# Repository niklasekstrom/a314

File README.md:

# A314

## What is it?

*A314* is a family of expansions for Amiga computers that lets a Raspberry Pi
(RPi) be used as a co-processor to the Amiga.

The Amiga and the RPi communicate through a shared memory that resides on the
A314 board. A communication protocol is implemented on top of the shared memory,
that allows programs on the Amiga to establish logical communication channels to
*services* running on the RPi. The protocol is handled by drivers on each side,
[*a314.device*](Software/a314device) on the Amiga and [*a314d*](Software/a314d)
on the RPi. The drivers are responsible for multiplexing packets from the logical
channels and notifying the receiving side when a packet is available, using interrupts.

## Hardware variants

Initially there was a single variant of A314 that connected to the trapdoor
on an Amiga 500. Since then several more variants have been developed for
different Amiga models. The same software run on the different hardware variants.

The design files for the different hardware variants are available in separate
repositories. The currently available variants are:

| Variant | Amiga model | Connector | GitHub repository |
|---------|-------------|-----------|-------------------|
| A314-500 | Amiga 500 | Trapdoor | <https://github.com/Eriond/A314-500-PCB> |
| A314-600 | Amiga 600 | Trapdoor | <https://github.com/Eriond/A314-600-PCB> |
| A314-1000 | Amiga 1000 | Front expansion | <https://github.com/Eriond/A314-1000-PCB> |
| A314-cp | Any Amiga with clockport | Clockport | <https://github.com/niklasekstrom/clockport_pi_interface> <br/> <https://github.com/Eriond/clockport_pi_interface> (alternative PCB layout) |

|         |            |
| ------------- |---------------|
|  |  |
|  |  |

The A314 software has also been adapted to run on the Musashi version of
[PiStorm](https://github.com/captain-amygdala/pistorm).

## What can you do with it today?

We have implemented a few services that run on the RPi and on the Amiga:

- [*a314fs*](Software/a314fs) is a file system that is mounted in AmigaDOS as the PI0: device.
The volume in PI0: is called PiDisk:, and is mapped to a directory in the RPi.

- [*pi*](Software/picmd) is a command that lets you invoke executables on the RPi from the AmigaDOS CLI. For example, if your current working directory is on PiDisk: and you run `pi vc hello.c -o hello`, then the vc program (the VBCC cross-compiler) is executed on the RPi with the given arguments. It will cross-compile `hello.c` into the Amiga executable file `hello`. The resulting binary is immediately accessible through the a314fs.  
You may also launch Interactive applications using the pi command, such as `pi mc -a` which will run Midnight Commander. Running pi without any arguments is equivalent to `pi bash` and will present you with a bash prompt from the RPi.

|         |            |
| ------------- |---------------|
|   |  |

- [*PiAudio*](Software/piaudio) lets the RPi stream audio samples directly to the shared chip memory, from where Paula plays those samples. PiAudio is integrated with [ALSA](https://www.alsa-project.org) on the RPi so that any program that plays audio through ALSA can be used, i.e. "pi mpg123 -a amiga song.mp3" plays song.mp3 using the program mpg123 to the Amiga.

- [*RemoteWB*](Software/remotewb) works by moving the Workbench bitplanes over to the chip memory on the A314. This requires that the A500 has at least a 8372 Agnus. During drawing of each frame on the Amiga, the RPi reads those bitplanes, encodes them into a [GIF image](Software/bpls2gif), and transmits that image to a web browser through a web socket. The web browser in turn, returns key presses and mouse movements back to the Amiga through the same web socket. In effect, this becomes a web browser based remote control application, comparable to VNC but with near zero performance impact on the Amiga CPU!

- [*VideoPlayer*](Software/videoplayer) is a simple program that displays a sequence of images on the A500 by letting the RPi write bitplanes directly to the shared memory (this again requires that the A314 memory is chip memory, and not "ranger" memory).

- [*a314eth.device*](Software/ethernet) is a SANA-II driver that forwards Ethernet packets to the network interface of the RPi. Together with an Amiga TCP/IP stack this provides network access to the Amiga.

- [*a314disk.device*](Software/disk) mounts an ADF or HDF file on the RPi as a disk drive on the Amiga.

- [*PiHid*](Software/hid) takes input events from mouse and keyboard that are
connected to the RPI with USB, and forwards those input events to input.device
in the Amiga.

- [*PiStats*](Software/pistats) displays live Raspberry Pi statistics on the Amiga, including per-core CPU usage, memory, kernel version, and root filesystem usage. It supports console output and graphical interfaces.

- [*a314sh*](Software/a314sh) lets you run AmigaDOS commands from the Raspberry Pi. Its Amiga-side daemon keeps a persistent shell context and returns command output and status to the Pi.

## What could it potentially be used for in the future?

Here are some services that we have considered but not gotten around to implement:

- Networking through a *bsdsocket.library* implementation that forwards socket operations to the RPi and executes those operations there. This would give a higher degree of offloading than using the SANA-II driver with a TCP/IP stack running on the Amiga. The start of such a service is available
in the `libremote` branch.

- Your ideas?

## Do you want to get involved?

If this sounds interesting, you'll probably want an A314 of your own to play with.
All the information needed to build boards is freely available in the hardware
GitHub repositories linked to above.

The source code for the A314 software that runs on the Amiga and on the RPi is
available in the [Software](Software) directory.

There is a Discord server for discussing A314. [Here's the invite link](https://discord.gg/TGZNKnA).

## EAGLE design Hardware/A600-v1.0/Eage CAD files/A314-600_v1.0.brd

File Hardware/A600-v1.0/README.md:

# A314-600 PCB v1.0

## Changelog

Initial commit of the **Amiga 600** version of the A314 board. Main differences compared to the Amiga 500 version:
 - 2MB chipRAM available as A314 shared memory (Disables the motherboard RAM)
 - Mechanical restrictions of the expansion bay implies Raspberry *Zero* form factor. The low power consumption and more generous voltage tolerances of the Zero* allowed for a simpler design, elliminating the 5V DC/DC converter (IC11 & Co.). 
 *see: https://raspberry-projects.com/pi/pi-hardware/raspberry-pi-zero/raspberry-pi-zero-hardware-general-specifications
  - Replacement LED board included. Allows for distinction between HardDrive and A314 activity on the same LED (Bi-colour)
 - Original LED overlay. If you don't want to use the included replacement LED board, then use your existing one, but connect it through the A314! A314 activity is then multiplexed on the HDD LED.
## Notes
This PCB has NPT milled slots with a narrow width (1.5mm) which some board houses won't accept. I have successfully used WellPCB with excellent results. Check with you favourite board house if they accept such narrow slots, before submitting a job.
At the moment of writing, AllPCB and JLCPCB could not handle this PCB. This may change in the future.

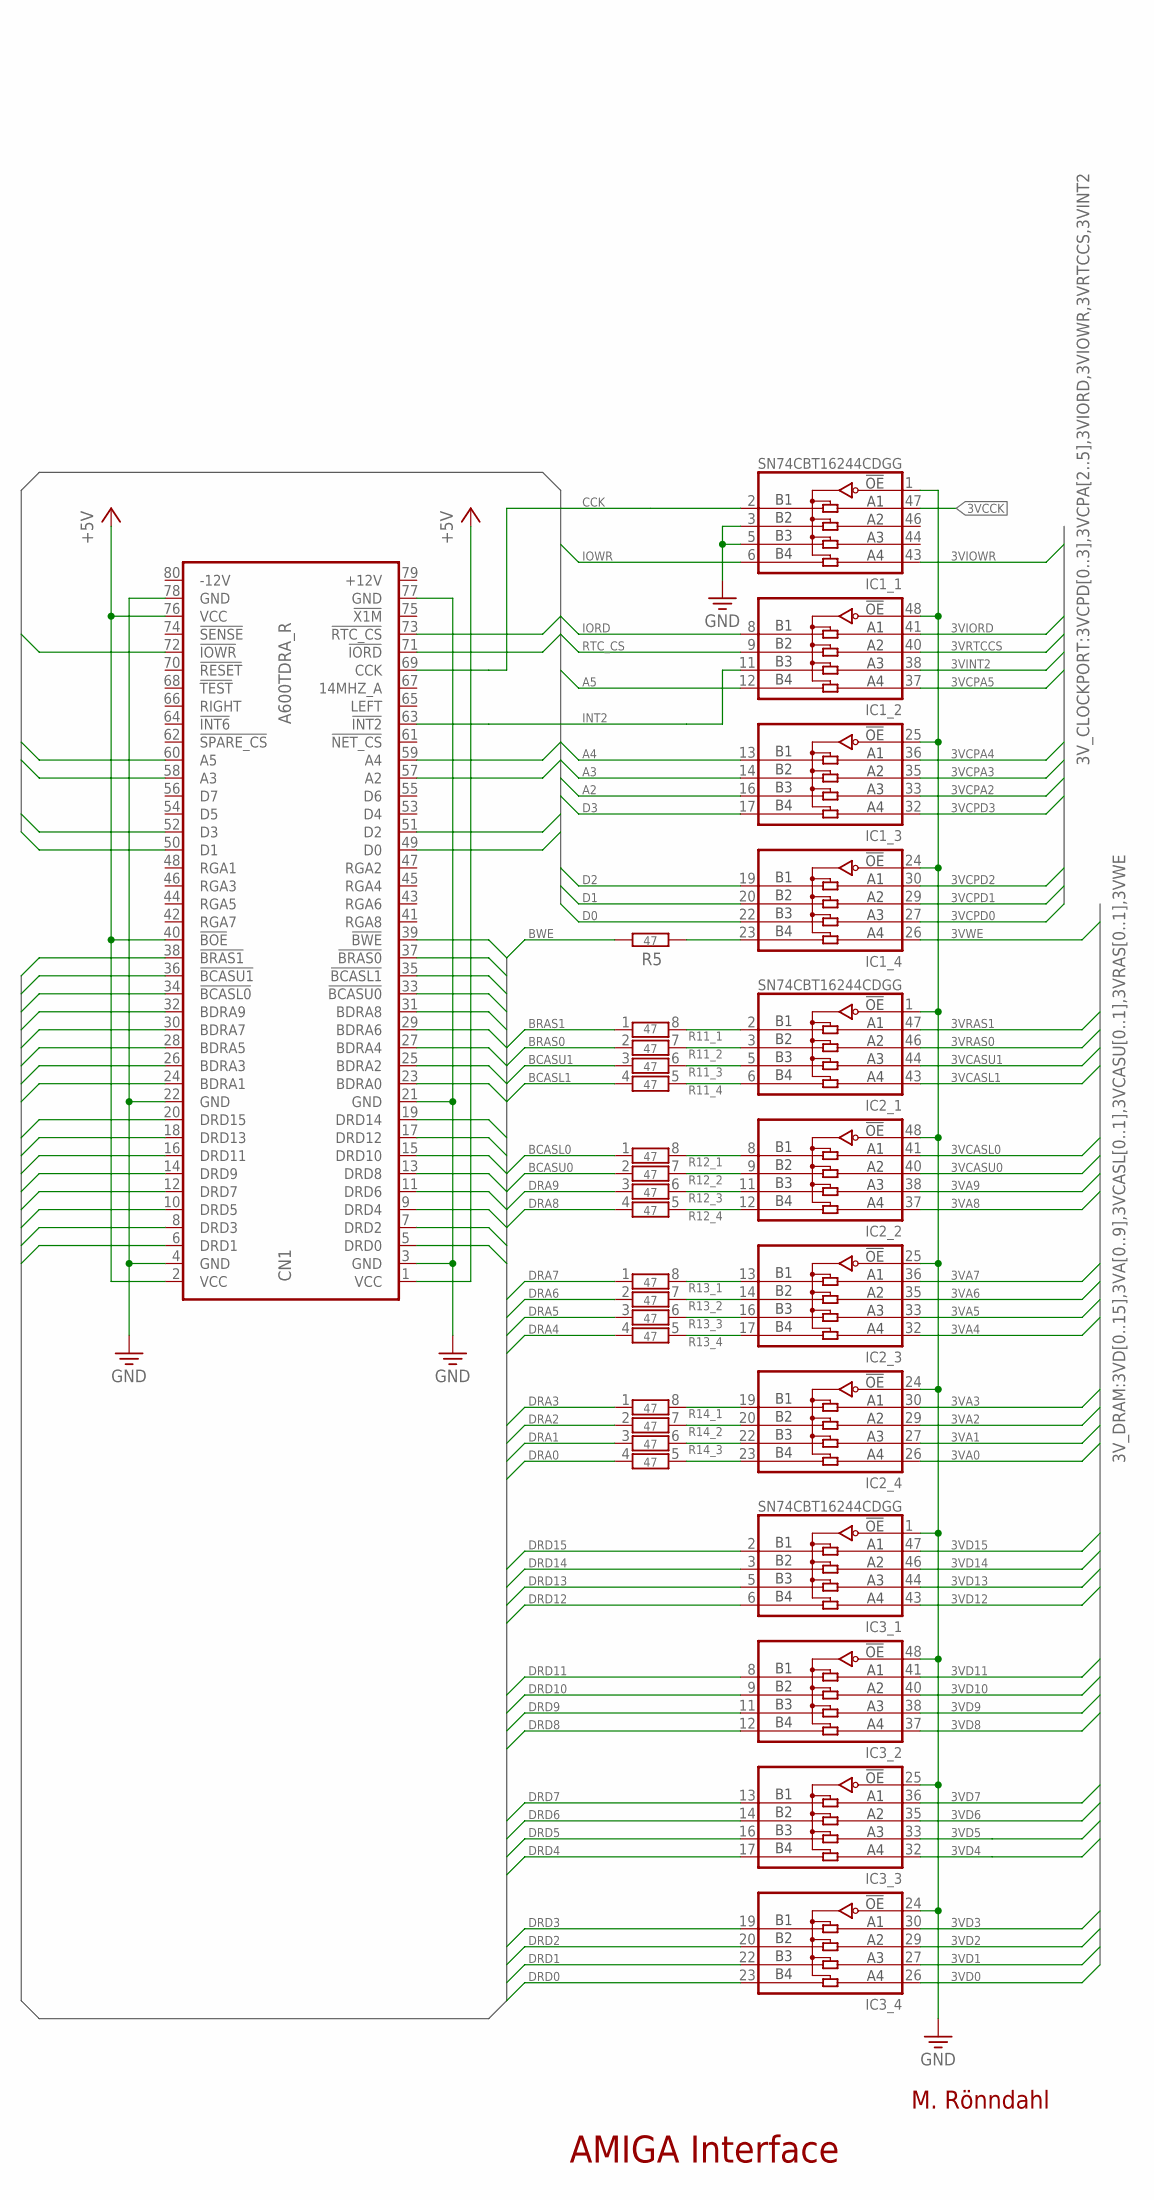
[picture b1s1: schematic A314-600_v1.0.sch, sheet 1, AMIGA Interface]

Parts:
CN1: A600TDRA_R; CE-2X40_1.27_R
IC1, IC2, IC3: SN74CBT16244CDGG; PSOP-DGG48
R5: 47; R0603
R11, R12, R13, R14: 47; CTS742C083

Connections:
3VA0: IC2.26 (A4); also elsewhere on the board
3VA1: IC2.27 (A3); also elsewhere on the board
3VA2: IC2.29 (A2); also elsewhere on the board
3VA3: IC2.30 (A1); also elsewhere on the board
3VA4: IC2.32 (A4); also elsewhere on the board
3VA5: IC2.33 (A3); also elsewhere on the board
3VA6: IC2.35 (A2); also elsewhere on the board
3VA7: IC2.36 (A1); also elsewhere on the board
3VA8: IC2.37 (A4); also elsewhere on the board
3VA9: IC2.38 (A3); also elsewhere on the board
3VCASL0: IC2.41 (A1); also elsewhere on the board
3VCASL1: IC2.43 (A4); also elsewhere on the board
3VCASU0: IC2.40 (A2); also elsewhere on the board
3VCASU1: IC2.44 (A3); also elsewhere on the board
3VCCK: IC1.47 (A1); also elsewhere on the board
3VCPA2: IC1.33 (A3); also elsewhere on the board
3VCPA3: IC1.35 (A2); also elsewhere on the board
3VCPA4: IC1.36 (A1); also elsewhere on the board
3VCPA5: IC1.37 (A4); also elsewhere on the board
3VCPD0: IC1.27 (A3); also elsewhere on the board
3VCPD1: IC1.29 (A2); also elsewhere on the board
3VCPD2: IC1.30 (A1); also elsewhere on the board
3VCPD3: IC1.32 (A4); also elsewhere on the board
3VD0: IC3.26 (A4); also elsewhere on the board
3VD1: IC3.27 (A3); also elsewhere on the board
3VD2: IC3.29 (A2); also elsewhere on the board
3VD3: IC3.30 (A1); also elsewhere on the board
3VD4: IC3.32 (A4); also elsewhere on the board
3VD5: IC3.33 (A3); also elsewhere on the board
3VD6: IC3.35 (A2); also elsewhere on the board
3VD7: IC3.36 (A1); also elsewhere on the board
3VD8: IC3.37 (A4); also elsewhere on the board
3VD9: IC3.38 (A3); also elsewhere on the board
3VD10: IC3.40 (A2); also elsewhere on the board
3VD11: IC3.41 (A1); also elsewhere on the board
3VD12: IC3.43 (A4); also elsewhere on the board
3VD13: IC3.44 (A3); also elsewhere on the board
3VD14: IC3.46 (A2); also elsewhere on the board
3VD15: IC3.47 (A1); also elsewhere on the board
3VINT2: IC1.38 (A3); also elsewhere on the board
3VIORD: IC1.41 (A1); also elsewhere on the board
3VIOWR: IC1.43 (A4); also elsewhere on the board
3VRAS0: IC2.46 (A2); also elsewhere on the board
3VRAS1: IC2.47 (A1); also elsewhere on the board
3VRTCCS: IC1.40 (A2); also elsewhere on the board
3VWE: IC1.26 (A4); also elsewhere on the board
+5V: CN1.1 (VCC), CN1.2 (VCC), CN1.40 (!BOE), CN1.76 (VCC); also elsewhere on the board
A2: CN1.57 (A2), IC1.16 (B3)
A3: CN1.58 (A3), IC1.14 (B2)
A4: CN1.59 (A4), IC1.13 (B1)
A5: CN1.60 (A5), IC1.12 (B4)
BCASL0: CN1.34 (!BCASL0), R12.1
BCASL1: CN1.35 (!BCASL1), R11.4
BCASU0: CN1.33 (!BCASU0), R12.2
BCASU1: CN1.36 (!BCASU1), R11.3
BRAS0: CN1.37 (!BRAS0), R11.2
BRAS1: CN1.38 (!BRAS1), R11.1
BWE: CN1.39 (!BWE), R5.1
CCK: CN1.69 (CCK), IC1.2 (B1)
D0: CN1.49 (D0), IC1.22 (B3)
D1: CN1.50 (D1), IC1.20 (B2)
D2: CN1.51 (D2), IC1.19 (B1)
D3: CN1.52 (D3), IC1.17 (B4)
DRA0: CN1.23 (BDRA0), R14.4
DRA1: CN1.24 (BDRA1), R14.3
DRA2: CN1.25 (BDRA2), R14.2
DRA3: CN1.26 (BDRA3), R14.1
DRA4: CN1.27 (BDRA4), R13.4
DRA5: CN1.28 (BDRA5), R13.3
DRA6: CN1.29 (BDRA6), R13.2
DRA7: CN1.30 (BDRA7), R13.1
DRA8: CN1.31 (BDRA8), R12.4
DRA9: CN1.32 (BDRA9), R12.3
DRD0: CN1.5 (DRD0), IC3.23 (B4)
DRD1: CN1.6 (DRD1), IC3.22 (B3)
DRD2: CN1.7 (DRD2), IC3.20 (B2)
DRD3: CN1.8 (DRD3), IC3.19 (B1)
DRD4: CN1.9 (DRD4), IC3.17 (B4)
DRD5: CN1.10 (DRD5), IC3.16 (B3)
DRD6: CN1.11 (DRD6), IC3.14 (B2)
DRD7: CN1.12 (DRD7), IC3.13 (B1)
DRD8: CN1.13 (DRD8), IC3.12 (B4)
DRD9: CN1.14 (DRD9), IC3.11 (B3)
DRD10: CN1.15 (DRD10), IC3.9 (B2)
DRD11: CN1.16 (DRD11), IC3.8 (B1)
DRD12: CN1.17 (DRD12), IC3.6 (B4)
DRD13: CN1.18 (DRD13), IC3.5 (B3)
DRD14: CN1.19 (DRD14), IC3.3 (B2)
DRD15: CN1.20 (DRD15), IC3.2 (B1)
GND: CN1.3 (GND), CN1.4 (GND), CN1.21 (GND), CN1.22 (GND), CN1.77 (GND), CN1.78 (GND), IC1.1 (!OE), IC1.3 (B2), IC1.5 (B3), IC1.24 (!OE), IC1.25 (!OE), IC1.48 (!OE), IC2.1 (!OE), IC2.24 (!OE), IC2.25 (!OE), IC2.48 (!OE), IC3.1 (!OE), IC3.24 (!OE), IC3.25 (!OE), IC3.48 (!OE); also elsewhere on the board
INT2: CN1.63 (!INT2), IC1.11 (B3)
IORD: CN1.71 (!IORD), IC1.8 (B1)
IOWR: CN1.72 (!IOWR), IC1.6 (B4)
unnamed: IC2.23 (B4), R14.5
unnamed: IC2.22 (B3), R14.6
unnamed: IC2.20 (B2), R14.7
unnamed: IC2.19 (B1), R14.8
unnamed: IC2.17 (B4), R13.5
unnamed: IC2.16 (B3), R13.6
unnamed: IC2.14 (B2), R13.7
unnamed: IC2.13 (B1), R13.8
unnamed: IC2.12 (B4), R12.5
unnamed: IC2.11 (B3), R12.6
unnamed: IC2.9 (B2), R12.7
unnamed: IC2.8 (B1), R12.8
unnamed: IC2.6 (B4), R11.5
unnamed: IC2.5 (B3), R11.6
unnamed: IC2.3 (B2), R11.7
unnamed: IC2.2 (B1), R11.8
unnamed: IC1.23 (B4), R5.2
RTC_CS: CN1.73 (!RTC_CS), IC1.9 (B2)

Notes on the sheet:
AMIGA Interface
M. Rönndahl

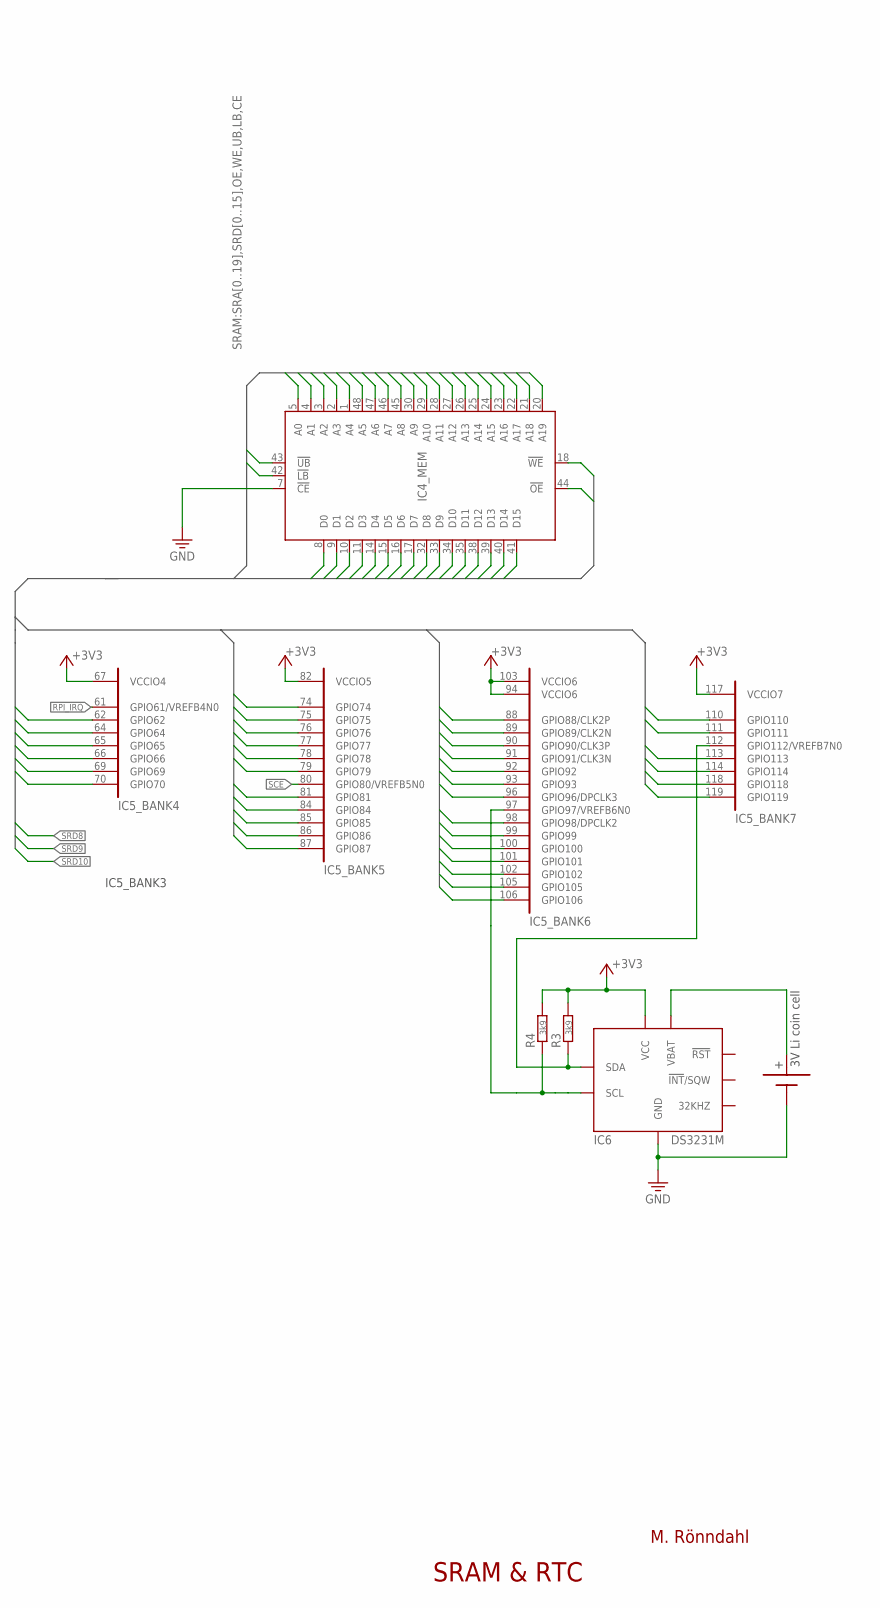
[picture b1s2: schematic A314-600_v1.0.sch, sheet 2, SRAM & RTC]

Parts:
BAT1: CR2025/CR2032TH; LINX20XX-THM
IC4: IS61WV102416FBLL-TLI; TSOP-1_48L_12X20
IC5: 10M08SCE144; SQFP-S-20X20-144
IC6: DS3231M; SOIC8
R3, R4: 3k9; R0603

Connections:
+: BAT1.+@1 (+), BAT1.+@2 (+), BAT1.+@3 (+), BAT1.+@4 (+), IC6.6 (VBAT)
+3V3: IC5.67 (VCCIO4), IC5.82 (VCCIO5), IC5.94 (VCCIO6), IC5.103 (VCCIO6), IC5.117 (VCCIO7), IC6.2 (VCC), R3.2, R4.2; also elsewhere on the board
GND: BAT1.GND (-), IC4.7 (!CE), IC6.5 (GND); also elsewhere on the board
LB: IC4.42 (!LB), IC5.79 (GPIO79)
OE: IC4.44 (!OE), IC5.84 (GPIO84)
RPI_IRQ: IC5.61 (GPIO61/VREFB4N0); also elsewhere on the board
RTC_SCL: IC5.97 (GPIO97/VREFB6N0), IC6.8 (SCL), R4.1
RTC_SDA: IC5.112 (GPIO112/VREFB7N0), IC6.7 (SDA), R3.1
SCE: IC5.80 (GPIO80/VREFB5N0); also elsewhere on the board
SRA0: IC4.5 (A0), IC5.93 (GPIO93)
SRA1: IC4.4 (A1), IC5.92 (GPIO92)
SRA2: IC4.3 (A2), IC5.91 (GPIO91/CLK3N)
SRA3: IC4.2 (A3), IC5.90 (GPIO90/CLK3P)
SRA4: IC4.1 (A4), IC5.89 (GPIO89/CLK2N)
SRA5: IC4.48 (A5), IC5.88 (GPIO88/CLK2P)
SRA6: IC4.47 (A6), IC5.87 (GPIO87)
SRA7: IC4.46 (A7), IC5.86 (GPIO86)
SRA8: IC4.45 (A8), IC5.85 (GPIO85)
SRA9: IC4.30 (A9), IC5.62 (GPIO62)
SRA10: IC4.29 (A10), IC5.64 (GPIO64)
SRA11: IC4.28 (A11), IC5.65 (GPIO65)
SRA12: IC4.27 (A12), IC5.66 (GPIO66)
SRA13: IC4.26 (A13), IC5.69 (GPIO69)
SRA14: IC4.25 (A14), IC5.70 (GPIO70)
SRA15: IC4.24 (A15), IC5.110 (GPIO110)
SRA16: IC4.23 (A16), IC5.111 (GPIO111)
SRA17: IC4.22 (A17), IC5.113 (GPIO113)
SRA18: IC4.21 (A18), IC5.114 (GPIO114)
SRA19: IC4.20 (A19), IC5.118 (GPIO118)
SRD0: IC4.8 (D0), IC5.96 (GPIO96/DPCLK3)
SRD1: IC4.9 (D1), IC5.98 (GPIO98/DPCLK2)
SRD2: IC4.10 (D2), IC5.99 (GPIO99)
SRD3: IC4.11 (D3), IC5.100 (GPIO100)
SRD4: IC4.14 (D4), IC5.101 (GPIO101)
SRD5: IC4.15 (D5), IC5.102 (GPIO102)
SRD6: IC4.16 (D6), IC5.105 (GPIO105)
SRD7: IC4.17 (D7), IC5.106 (GPIO106)
SRD8: IC4.32 (D8); also elsewhere on the board
SRD9: IC4.33 (D9); also elsewhere on the board
SRD10: IC4.34 (D10); also elsewhere on the board
SRD11: IC4.35 (D11), IC5.74 (GPIO74)
SRD12: IC4.38 (D12), IC5.75 (GPIO75)
SRD13: IC4.39 (D13), IC5.76 (GPIO76)
SRD14: IC4.40 (D14), IC5.77 (GPIO77)
SRD15: IC4.41 (D15), IC5.78 (GPIO78)
UB: IC4.43 (!UB), IC5.81 (GPIO81)
WE: IC4.18 (!WE), IC5.119 (GPIO119)

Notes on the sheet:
IC5_BANK3
SRAM & RTC
3V Li coin cell
M. Rönndahl

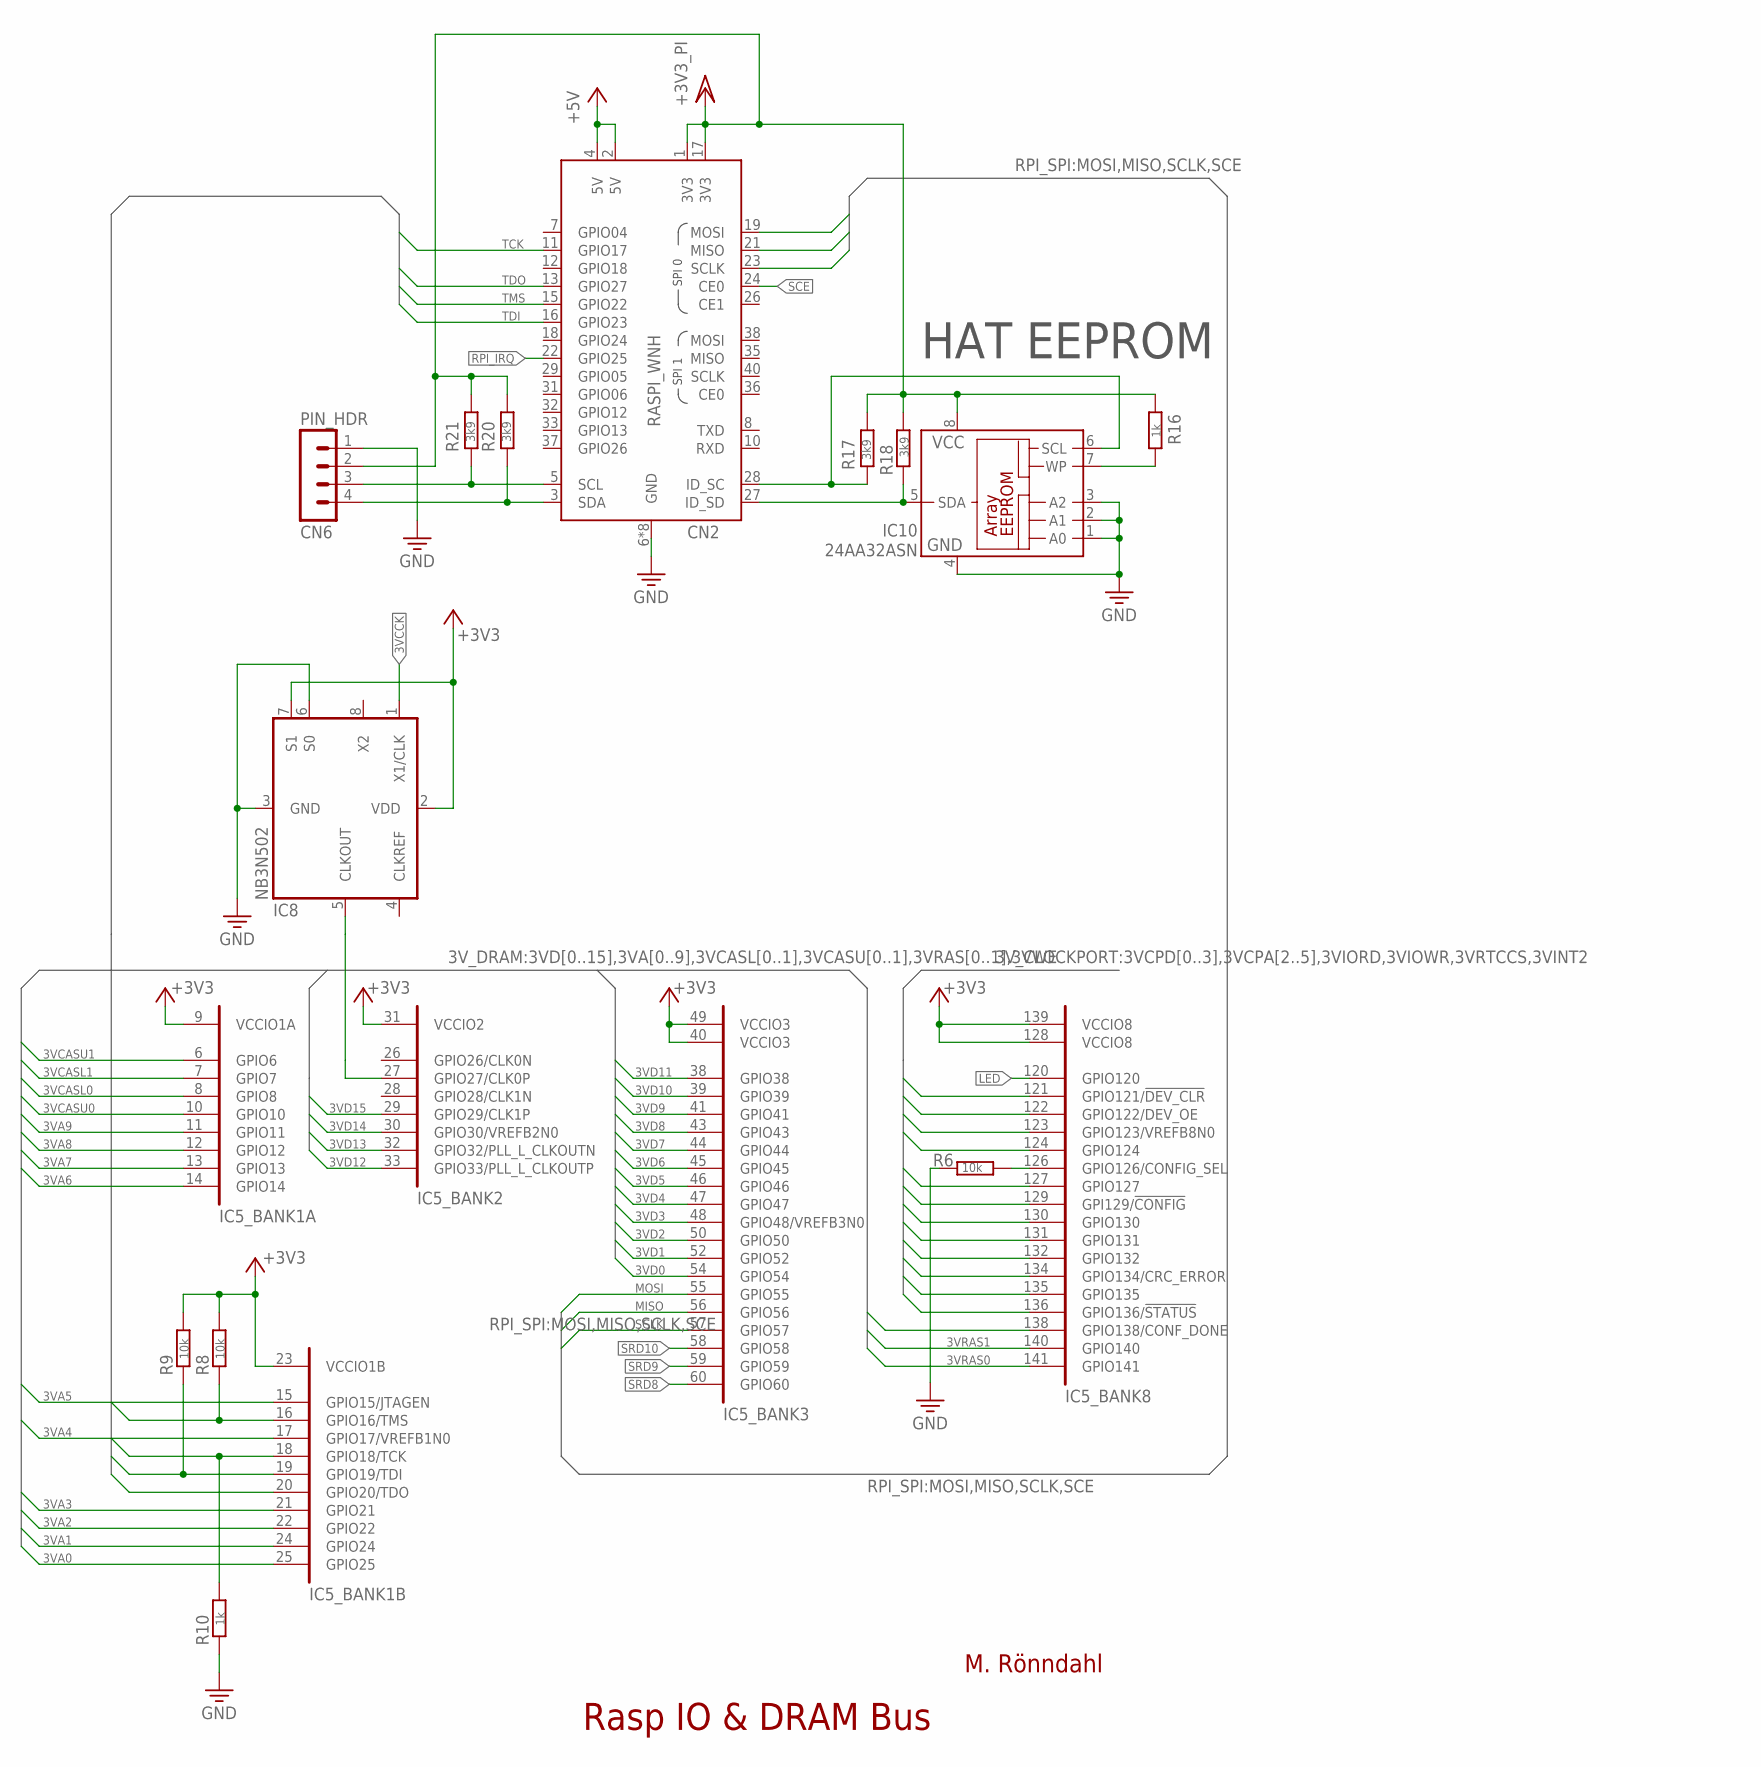
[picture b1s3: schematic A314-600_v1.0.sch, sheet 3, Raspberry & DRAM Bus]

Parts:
CN2: RASPI_WNH; RASPBERRYPIZEROW_NO_HOLES
CN6: PIN_HDR; MA04-1
IC5: 10M08SCE144; SQFP-S-20X20-144
IC8: NB3N502; SO08
IC10: 24AA32ASN; SO-08
R6, R8, R9: 10k; R0603
R10, R16: 1k; R0603
R17, R18, R20, R21: 3k9; R0603

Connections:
3VA0: IC5.25 (GPIO25); also elsewhere on the board
3VA1: IC5.24 (GPIO24); also elsewhere on the board
3VA2: IC5.22 (GPIO22); also elsewhere on the board
3VA3: IC5.21 (GPIO21); also elsewhere on the board
3VA4: IC5.17 (GPIO17/VREFB1N0); also elsewhere on the board
3VA5: IC5.15 (GPIO15/JTAGEN); also elsewhere on the board
3VA6: IC5.14 (GPIO14); also elsewhere on the board
3VA7: IC5.13 (GPIO13); also elsewhere on the board
3VA8: IC5.12 (GPIO12); also elsewhere on the board
3VA9: IC5.11 (GPIO11); also elsewhere on the board
3VCASL0: IC5.8 (GPIO8); also elsewhere on the board
3VCASL1: IC5.7 (GPIO7); also elsewhere on the board
3VCASU0: IC5.10 (GPIO10); also elsewhere on the board
3VCASU1: IC5.6 (GPIO6); also elsewhere on the board
3VCCK: IC8.1 (X1/CLK); also elsewhere on the board
3VCPA2: IC5.131 (GPIO131); also elsewhere on the board
3VCPA3: IC5.130 (GPIO130); also elsewhere on the board
3VCPA4: IC5.129 (GPI129/!CONFIG); also elsewhere on the board
3VCPA5: IC5.127 (GPIO127); also elsewhere on the board
3VCPD0: IC5.136 (GPIO136/!STATUS); also elsewhere on the board
3VCPD1: IC5.135 (GPIO135); also elsewhere on the board
3VCPD2: IC5.134 (GPIO134/CRC_ERROR); also elsewhere on the board
3VCPD3: IC5.132 (GPIO132); also elsewhere on the board
3VD0: IC5.54 (GPIO54); also elsewhere on the board
3VD1: IC5.52 (GPIO52); also elsewhere on the board
3VD2: IC5.50 (GPIO50); also elsewhere on the board
3VD3: IC5.48 (GPIO48/VREFB3N0); also elsewhere on the board
3VD4: IC5.47 (GPIO47); also elsewhere on the board
3VD5: IC5.46 (GPIO46); also elsewhere on the board
3VD6: IC5.45 (GPIO45); also elsewhere on the board
3VD7: IC5.44 (GPIO44); also elsewhere on the board
3VD8: IC5.43 (GPIO43); also elsewhere on the board
3VD9: IC5.41 (GPIO41); also elsewhere on the board
3VD10: IC5.39 (GPIO39); also elsewhere on the board
3VD11: IC5.38 (GPIO38); also elsewhere on the board
3VD12: IC5.33 (GPIO33/PLL_L_CLKOUTP); also elsewhere on the board
3VD13: IC5.32 (GPIO32/PLL_L_CLKOUTN); also elsewhere on the board
3VD14: IC5.30 (GPIO30/VREFB2N0); also elsewhere on the board
3VD15: IC5.29 (GPIO29/CLK1P); also elsewhere on the board
3VINT2: IC5.124 (GPIO124); also elsewhere on the board
3VIORD: IC5.122 (GPIO122/DEV_OE); also elsewhere on the board
3VIOWR: IC5.121 (GPIO121/!DEV_CLR); also elsewhere on the board
3VRAS0: IC5.141 (GPIO141); also elsewhere on the board
3VRAS1: IC5.140 (GPIO140); also elsewhere on the board
3VRTCCS: IC5.123 (GPIO123/VREFB8N0); also elsewhere on the board
3VWE: IC5.138 (GPIO138/CONF_DONE); also elsewhere on the board
14MHZ: IC5.27 (GPIO27/CLK0P), IC8.5 (CLKOUT)
+3V3: IC5.9 (VCCIO1A), IC5.23 (VCCIO1B), IC5.31 (VCCIO2), IC5.40 (VCCIO3), IC5.49 (VCCIO3), IC5.128 (VCCIO8), IC5.139 (VCCIO8), IC8.2 (VDD), IC8.7 (S1), R8.2, R9.2; also elsewhere on the board
+5V: CN2.2 (5V), CN2.4 (5V); also elsewhere on the board
CONF_SEL: IC5.126 (GPIO126/CONFIG_SEL), R6.1
GND: CN2.6 (GND), CN2.9 (GND), CN2.14 (GND), CN2.20 (GND), CN2.25 (GND), CN2.30 (GND), CN2.34 (GND), CN2.39 (GND), CN6.1, IC8.3 (GND), IC8.6 (S0), IC10.1 (A0), IC10.2 (A1), IC10.3 (A2), IC10.4 (GND), R6.2, R10.1; also elsewhere on the board
HAT_SCL: CN2.28 (ID_SC), IC10.6 (SCL), R17.2
HAT_SDA: CN2.27 (ID_SD), IC10.5 (SDA), R18.1
LED: IC5.120 (GPIO120); also elsewhere on the board
MISO: CN2.21 (MISO), IC5.56 (GPIO56)
MOSI: CN2.19 (MOSI), IC5.55 (GPIO55)
PI_SCL: CN2.5 (SCL), CN6.3, R21.2
PI_SDA: CN2.3 (SDA), CN6.4, R20.2
RPI_IRQ: CN2.22 (GPIO25); also elsewhere on the board
SCE: CN2.24 (CE0); also elsewhere on the board
SCLK: CN2.23 (SCLK), IC5.57 (GPIO57)
SRD8: IC5.60 (GPIO60); also elsewhere on the board
SRD9: IC5.59 (GPIO59); also elsewhere on the board
SRD10: IC5.58 (GPIO58); also elsewhere on the board
TCK: CN2.11 (GPIO17), IC5.18 (GPIO18/TCK), R10.2
TDI: CN2.16 (GPIO23), IC5.19 (GPIO19/TDI), R9.1
TDO: CN2.13 (GPIO27), IC5.20 (GPIO20/TDO)
TMS: CN2.15 (GPIO22), IC5.16 (GPIO16/TMS), R8.1
VCC/2: CN2.1 (3V3), CN2.17 (3V3), CN6.2, IC10.8 (VCC), R16.2, R17.1, R18.2, R20.1, R21.1; also elsewhere on the board
WP: IC10.7 (WP), R16.1

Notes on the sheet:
Rasp IO & DRAM Bus
M. Rönndahl
HAT EEPROM

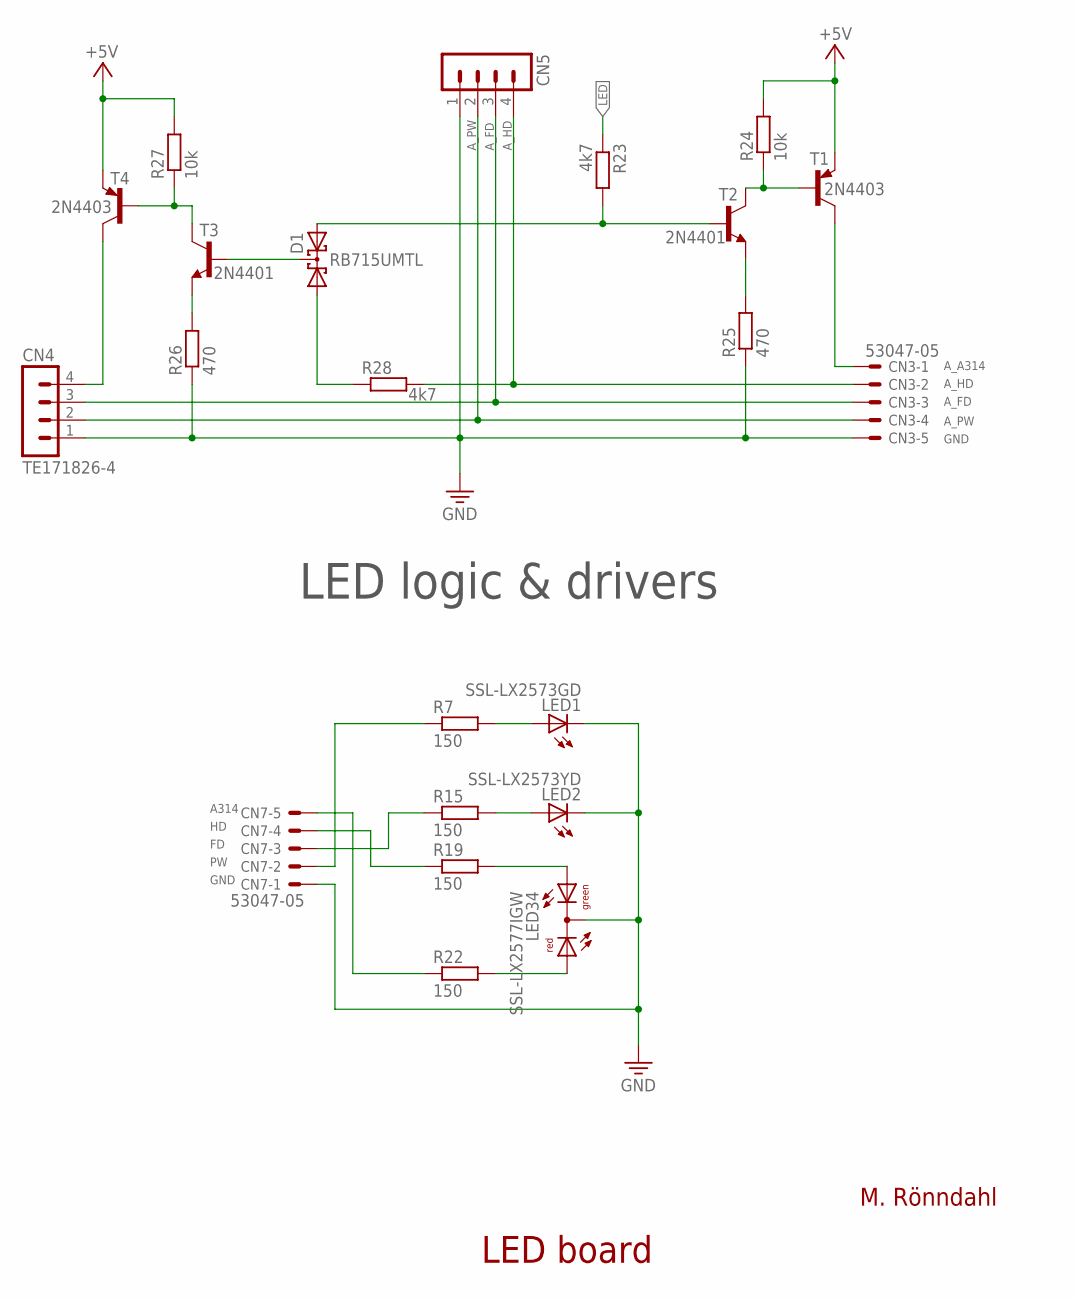
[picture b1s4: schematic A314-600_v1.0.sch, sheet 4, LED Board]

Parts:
CN3, CN7: 53047-05
CN4: TE171826-4; FLOPPY_PWR
CN5: MA04-1
D1: RB715UMTL; SOT23
LED1: SSL-LX2573GD; LED2X5
LED2: SSL-LX2573YD; LED2X5
LED34: SSL-LX2577IGW; DUOLED2X5
R7, R15, R19, R22: 150; R0603
R23, R28: 4k7; R0603
R24, R27: 10k; R0603
R25, R26: 470; R0603
T1, T4: 2N4403; SOT23-BEC
T2, T3: 2N4401; SOT23-BEC

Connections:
+5V: R24.2, R27.2, T1.E, T4.E; also elsewhere on the board
A314: CN7.5, R22.1
A_314: CN4.4, T4.C
A_A314: CN3.1, T1.C
A_FD: CN3.3, CN4.3, CN5.3
A_HD: CN3.2, CN5.4, R28.2
A_PW: CN3.4, CN4.2, CN5.2
FD: CN7.3, R15.1
GND: CN3.5, CN4.1, CN5.1, CN7.1, LED1.K (C), LED2.K (C), LED34.K (C), R25.1, R26.1; also elsewhere on the board
HD: CN7.4, R19.1
LED: R23.1; also elsewhere on the board
unnamed: LED1.A, R7.2
unnamed: LED2.A, R15.2
unnamed: D1.3 (C), T3.B
unnamed: D1.1 (A1), R28.1
unnamed: LED34.AG, R19.2
unnamed: LED34.AR, R22.2
unnamed: R25.2, T2.E
unnamed: R24.1, T1.B, T2.C
unnamed: R26.2, T3.E
unnamed: R27.1, T3.C, T4.B
PW: CN7.2, R7.1
R24_LED: D1.2 (A2), R23.2, T2.B

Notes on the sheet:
M. Rönndahl
LED board
LED logic & drivers

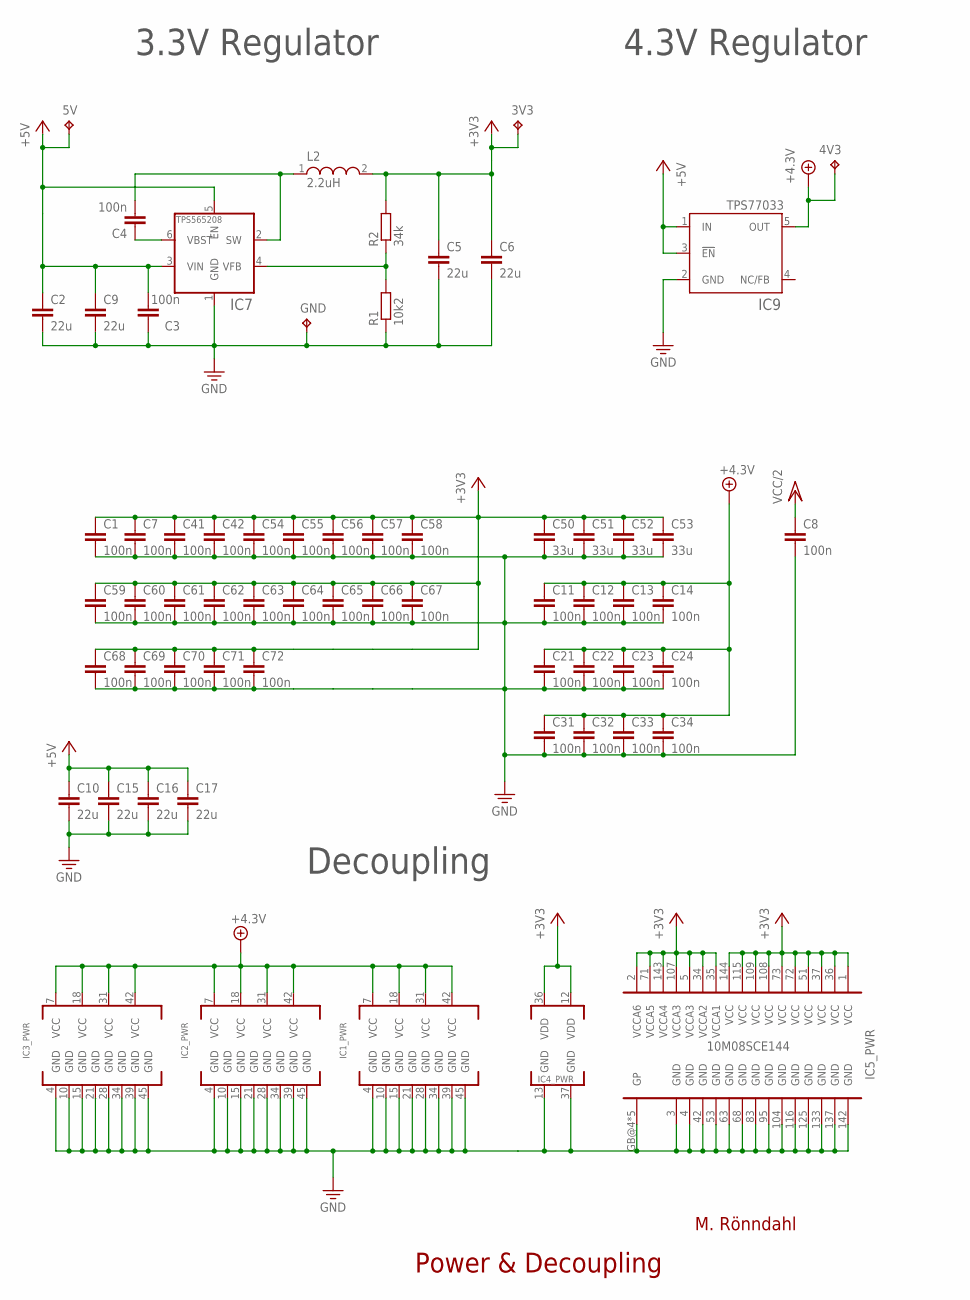
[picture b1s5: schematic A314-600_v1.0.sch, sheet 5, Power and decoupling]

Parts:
3V3, 4V3, 5V: TPPAD1-13; P1-13
C1, C3, C4, C7, C8, C11, C12, C13, C14, C21, C22, C23, C24, C31, C32, C33, C34, C41, C42, C54, C55, C56, C57, C58, C59, C60, C61, C62, C63, C64, C65, C66, C67, C68, C69, C70, C71, C72: 100n; C0603
C2, C5, C6, C9, C10, C15, C16, C17: 22u; C0805; MOUSER 810-CGA8P1X7R1E226M
C50, C51, C52, C53: 33u; C0805
GND: TPPAD1-13; P1-13
IC1, IC2, IC3: SN74CBT16244CDGG; PSOP-DGG48
IC4: IS61WV102416FBLL-TLI; TSOP-1_48L_12X20
IC5: 10M08SCE144; SQFP-S-20X20-144
IC7: TPS565208; THIN_SO23; MOUSER 595-TPS565208DDCR
IC9: TPS77033; SOT23-DBV
L2: 2.2uH; WE-TPC_1028/1038; MOUSER 710-7440650022
R1: 10k2; R0603
R2: 34k; R0603

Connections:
+3V3: 3V3.TP, C1.1, C5.1, C6.1, C7.1, C41.1, C42.1, C50.1, C51.1, C52.1, C53.1, C54.1, C55.1, C56.1, C57.1, C58.1, C59.1, C60.1, C61.1, C62.1, C63.1, C64.1, C65.1, C66.1, C67.1, C68.1, C69.1, C70.1, C71.1, C72.1, IC4.12 (VDD), IC4.36 (VDD), IC5.1 (VCC), IC5.2 (VCCA6), IC5.5 (VCCA3), IC5.34 (VCCA2), IC5.35 (VCCA1), IC5.36 (VCC), IC5.37 (VCC), IC5.51 (VCC), IC5.71 (VCCA5), IC5.72 (VCC), IC5.73 (VCC), IC5.107 (VCCA3), IC5.108 (VCC), IC5.109 (VCC), IC5.115 (VCC), IC5.143 (VCCA4), IC5.144 (VCC), L2.2, R2.2; also elsewhere on the board
+4.3V: 4V3.TP, C11.1, C12.1, C13.1, C14.1, C21.1, C22.1, C23.1, C24.1, C31.1, C32.1, C33.1, C34.1, IC1.7 (VCC), IC1.18 (VCC), IC1.31 (VCC), IC1.42 (VCC), IC2.7 (VCC), IC2.18 (VCC), IC2.31 (VCC), IC2.42 (VCC), IC3.7 (VCC), IC3.18 (VCC), IC3.31 (VCC), IC3.42 (VCC), IC9.5 (OUT)
+5V: 5V.TP, C2.1, C3.2, C9.1, C10.1, C15.1, C16.1, C17.1, IC7.3 (VIN), IC7.5 (EN), IC9.1 (IN), IC9.3 (!EN); also elsewhere on the board
BST1: C4.1, IC7.6 (VBST)
FB1: IC7.4 (VFB), R1.2, R2.1
GND: C1.2, C2.2, C3.1, C5.2, C6.2, C7.2, C8.2, C9.2, C10.2, C11.2, C12.2, C13.2, C14.2, C15.2, C16.2, C17.2, C21.2, C22.2, C23.2, C24.2, C31.2, C32.2, C33.2, C34.2, C41.2, C42.2, C50.2, C51.2, C52.2, C53.2, C54.2, C55.2, C56.2, C57.2, C58.2, C59.2, C60.2, C61.2, C62.2, C63.2, C64.2, C65.2, C66.2, C67.2, C68.2, C69.2, C70.2, C71.2, C72.2, GND.TP, IC1.4 (GND), IC1.10 (GND), IC1.15 (GND), IC1.21 (GND), IC1.28 (GND), IC1.34 (GND), IC1.39 (GND), IC1.45 (GND), IC2.4 (GND), IC2.10 (GND), IC2.15 (GND), IC2.21 (GND), IC2.28 (GND), IC2.34 (GND), IC2.39 (GND), IC2.45 (GND), IC3.4 (GND), IC3.10 (GND), IC3.15 (GND), IC3.21 (GND), IC3.28 (GND), IC3.34 (GND), IC3.39 (GND), IC3.45 (GND), IC4.13 (GND), IC4.37 (GND), IC5.3 (GND), IC5.4 (GND), IC5.42 (GND), IC5.53 (GND), IC5.63 (GND), IC5.68 (GND), IC5.83 (GND), IC5.95 (GND), IC5.104 (GND), IC5.116 (GND), IC5.125 (GND), IC5.133 (GND), IC5.137 (GND), IC5.142 (GND), IC5.GB@4 (GP), IC5.GP@1 (GP), IC5.GP@2 (GP), IC5.GP@3 (GP), IC5.GP@5 (GP), IC7.1 (GND), IC9.2 (GND), R1.1; also elsewhere on the board
SW: C4.2, IC7.2 (SW), L2.1
VCC/2: C8.1; also elsewhere on the board

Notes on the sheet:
Power & Decoupling
3.3V Regulator
4.3V Regulator
M. Rönndahl
Decoupling

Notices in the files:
HDL/a314.qsf:
Copyright (C) 2018  Intel Corporation. All rights reserved.
parts and their libraries:
Wurth_power_magnetics: Copyright: Würth Elektronik
